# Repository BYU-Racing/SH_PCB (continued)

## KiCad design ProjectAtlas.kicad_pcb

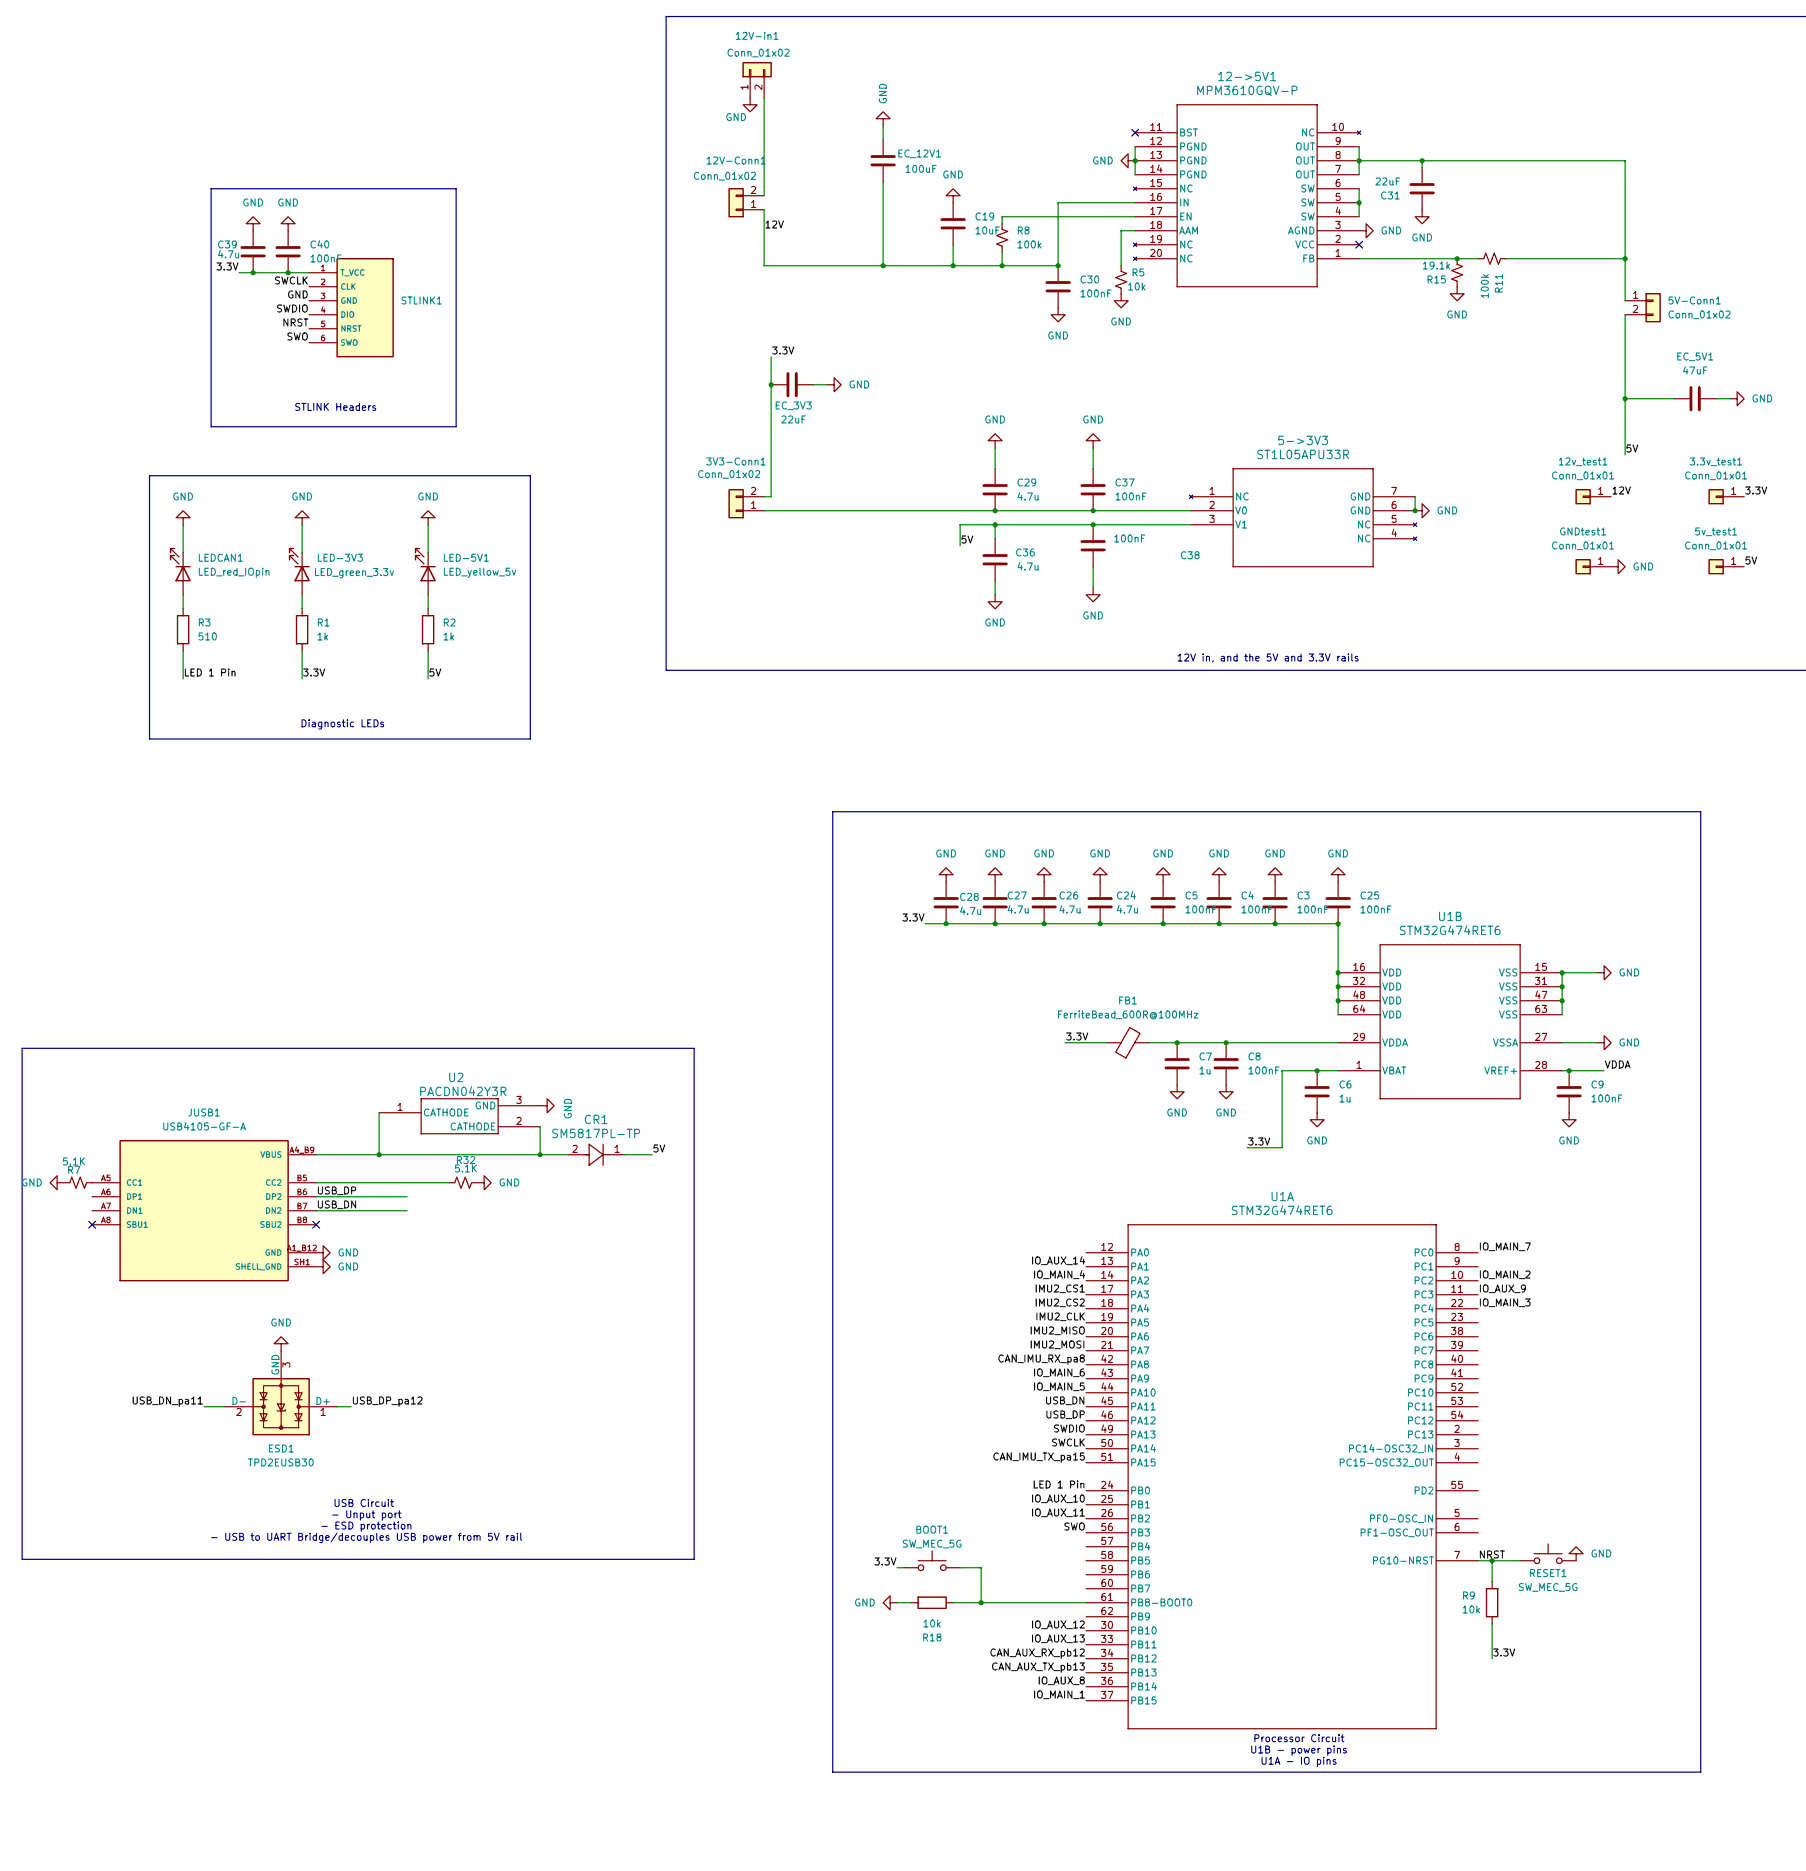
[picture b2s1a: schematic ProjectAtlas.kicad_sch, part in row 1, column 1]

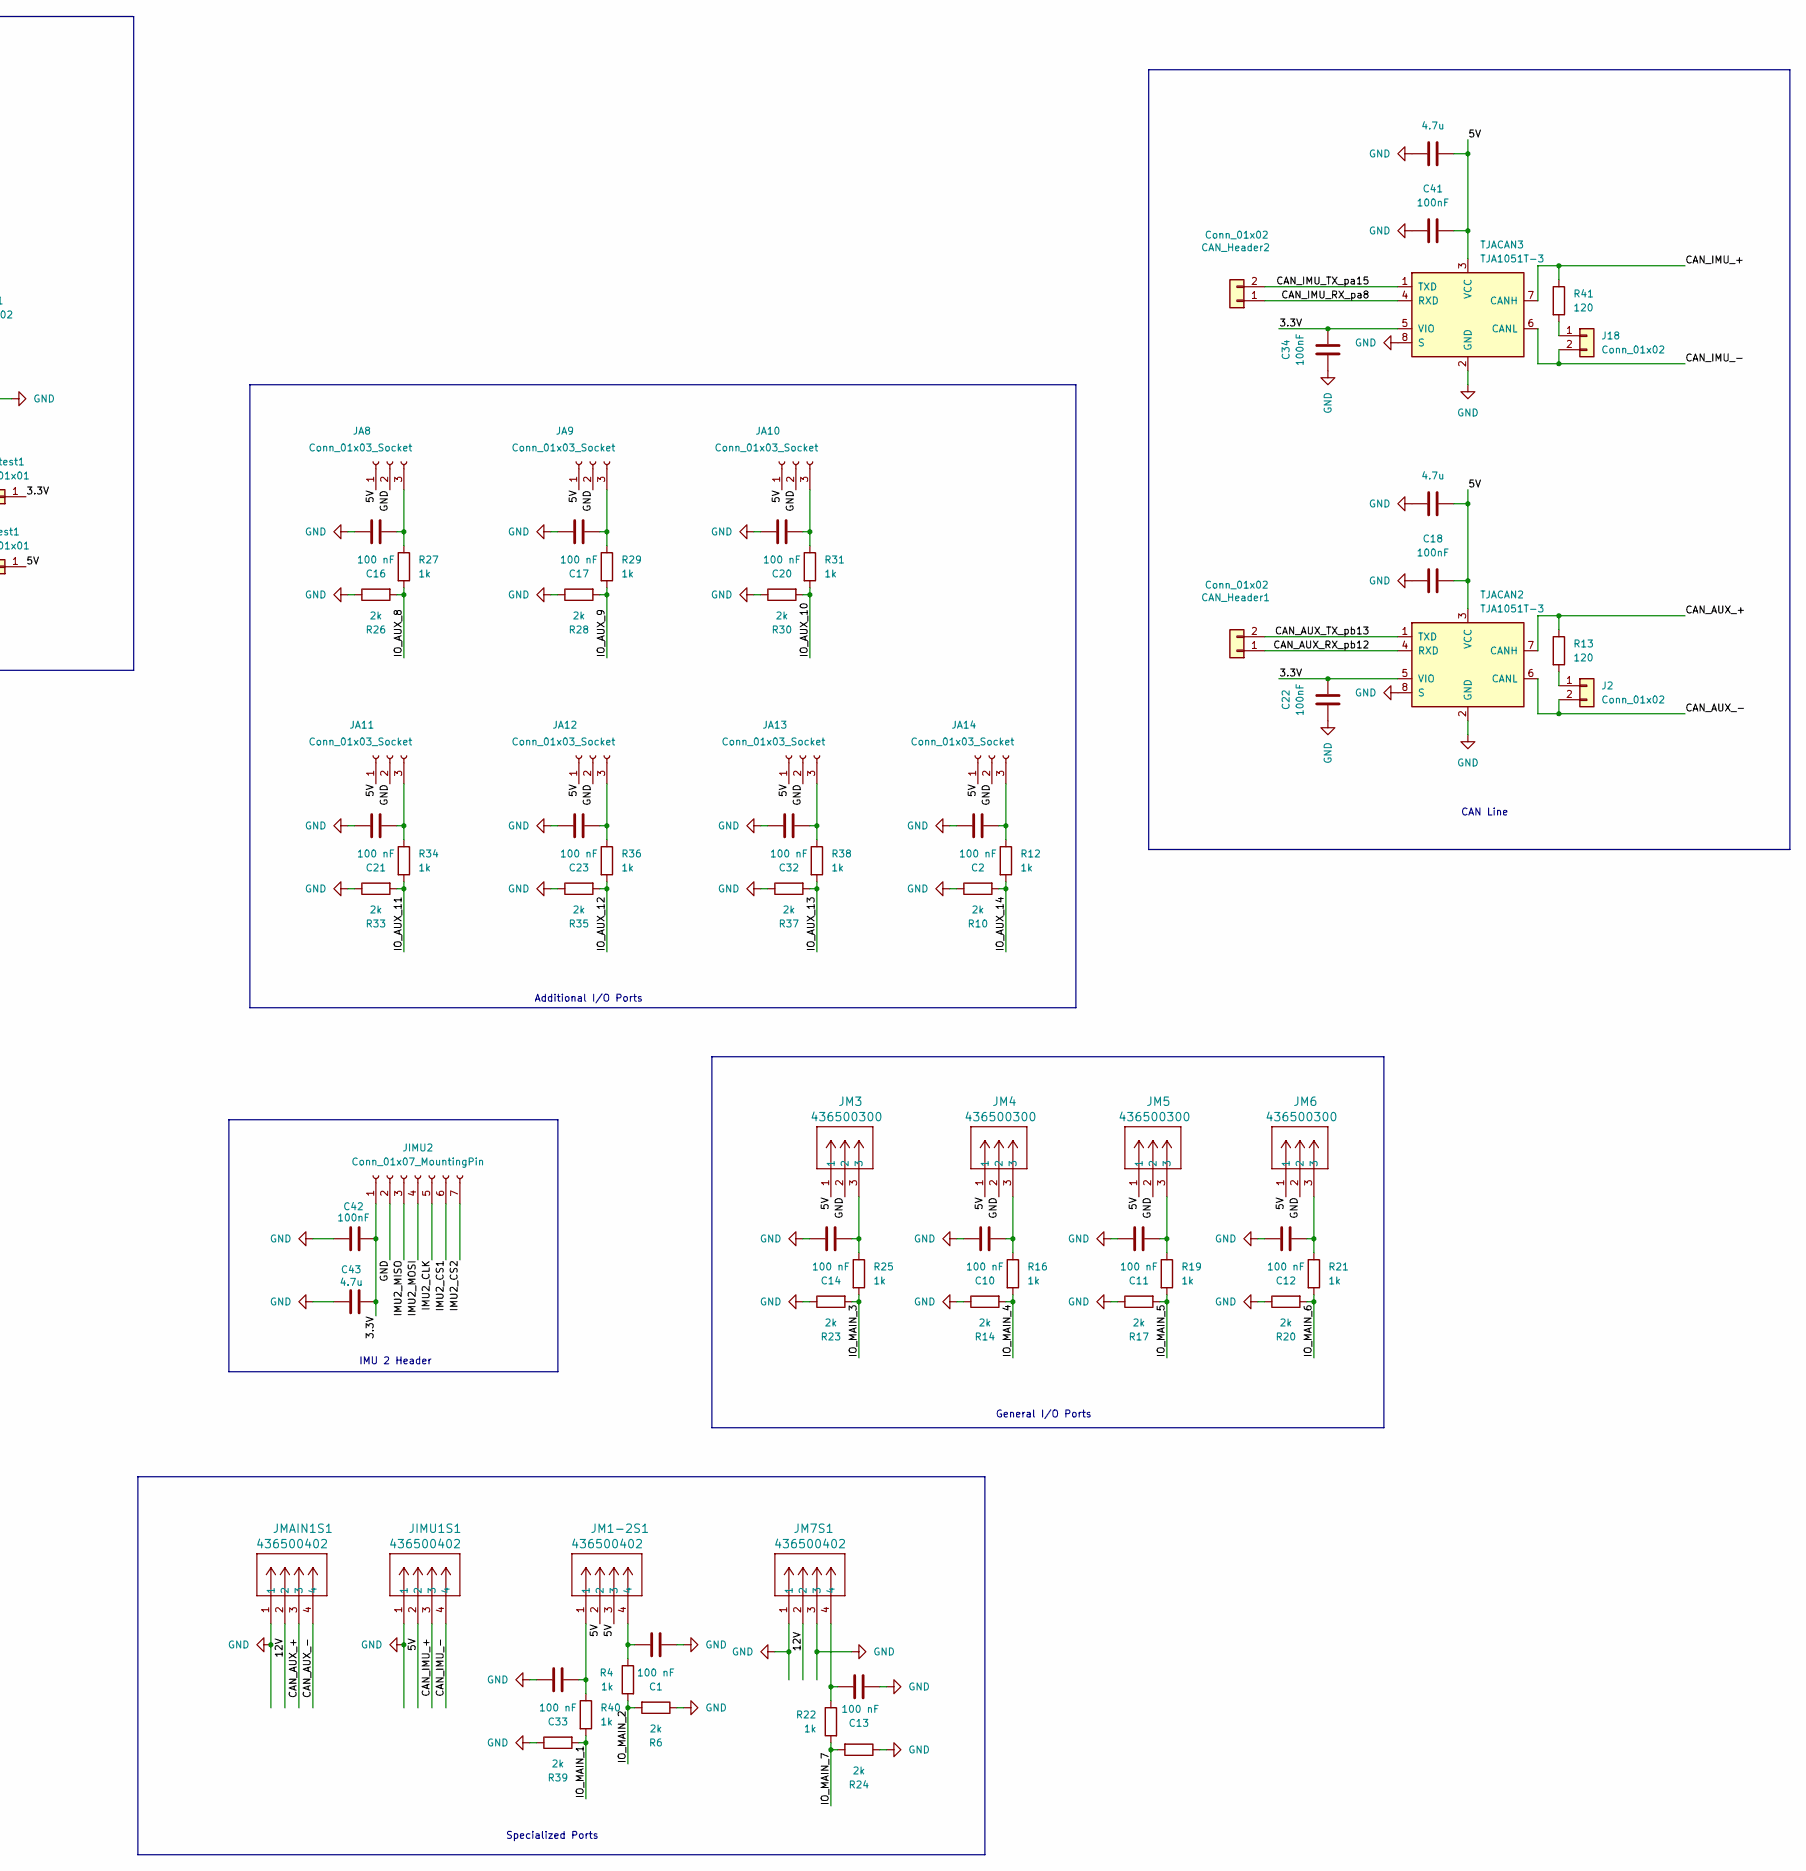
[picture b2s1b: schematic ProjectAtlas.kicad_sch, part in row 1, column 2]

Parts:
3.3v_test1, 5v_test1, 12v_test1: Conn_01x01; PinHeader_1x01_P2.54mm_Vertical
3V3-Conn1, 5V-Conn1, 12V-Conn1, 12V-in1: Conn_01x02; PinHeader_1x02_P2.54mm_Vertical
5->3V3: ST1L05APU33R; DFN_5APU33R_STM
12->5V1: MPM3610GQV-P
BOOT1: SW_MEC_5G; TS-1187A-B-A-B
C1, C2, C10, C11, C12, C13, C14, C16, C17, C20, C21, C23, C32, C33: 100 nF; CP_Axial_L10.0mm_D6.0mm_P15.00mm_Horizontal
C3, C4, C5, C8, C9, C18, C22, C25, C30, C34, C37, C38, C40, C41, C42: 100nF; C_0603_1608Metric
C6, C7: 1u; C_0805_2012Metric
C15, C24, C26, C27, C28, C29, C35, C36, C39, C43: 4.7u; C_0805_2012Metric
C19: 10uF; C_0805_2012Metric
C31: 22uF; C_0805_2012Metric
CAN_Header1, CAN_Header2: Conn_01x02; PinHeader_1x02_P2.54mm_Vertical
CR1: SM5817PL-TP
EC_3V3: 22uF; CP_Elec_4x5.4
EC_5V1: 47uF; CP_Elec_6.3x5.4
EC_12V1: 100uF; CP_Elec_8x10
ESD1: TPD2EUSB30; Texas_DRT-3
FB1: FerriteBead_600R@100MHz; GZ1608D601TF
GNDtest1: Conn_01x01; PinHeader_1x01_P2.54mm_Vertical
J2, J18: Conn_01x02; PinHeader_1x02_P2.54mm_Vertical
JA8, JA9, JA10, JA11, JA12, JA13, JA14: Conn_01x03_Socket; PinHeader_1x03_P2.00mm_Vertical
JIMU1S1: 436500402; CONN_SD-43650-001_04_MOL
JIMU2: Conn_01x07_MountingPin; PinHeader_1x07_P2.00mm_Vertical
JM1-2S1, JM7S1: 436500402; CONN_SD-43650-001_04_MOL
JM3, JM4, JM5, JM6: 436500300; CONN_SD-43650-001_03_MOL
JMAIN1S1: 436500402; CONN_SD-43650-001_04_MOL
JUSB1: USB4105-GF-A; GCT_USB4105-GF-A; PARTREV B4
LED-3V3: LED_green_3.3v; LED_0805_2012Metric
LED-5V1: LED_yellow_5v; LED_0805_2012Metric
LEDCAN1: LED_red_IOpin; LED_0805_2012Metric
R1, R2: 1k; R_0603_1608Metric
R3: 510; R_0603_1608Metric
R4, R12, R16, R19, R21, R22, R25, R27, R29, R31, R34, R36, R38, R40: 1k; R_Axial_DIN0204_L3.6mm_D1.6mm_P1.90mm_Vertical
R5, R9, R18: 10k; R_0603_1608Metric
R6, R10, R14, R17, R20, R23, R24, R26, R28, R30, R33, R35, R37, R39: 2k; R_Axial_DIN0204_L3.6mm_D1.6mm_P1.90mm_Vertical
R7, R32: 5.1K; R_0603_1608Metric
R8, R11: 100k; R_0603_1608Metric
R13, R41: 120; R_0603_1608Metric
R15: 19.1k; R_0603_1608Metric
RESET1: SW_MEC_5G; TS-1187A-B-A-B
STLINK1: PinHeader_1x06_P2.54mm_Vertical
TJACAN2, TJACAN3: TJA1051T-3; SOIC-8_3.9x4.9mm_P1.27mm
U1: STM32G474RET6; STM32G474RE
U2: PACDN042Y3R; SOT-23_ONS

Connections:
/3.3V: 3.3v_test1.1, 3V3-Conn1.2, BOOT1.3 (B), BOOT1.4 (B), C3.2, C4.2, C5.2, C6.1, C22.2, C24.2, C25.2, C26.2, C27.2, C28.2, C34.2, C39.2, C40.2, C42.2, C43.2, EC_3V3.1, FB1.1, JIMU2.1, R1.2, R9.1, STLINK1.1 (T_VCC), TJACAN2.5 (VIO), TJACAN3.5 (VIO), U1.1 (VBAT), U1.16 (VDD), U1.32 (VDD), U1.48 (VDD), U1.64 (VDD)
/5V: 5->3V3.3 (V1), 5V-Conn1.2, 5v_test1.1, C15.2, C18.2, C35.2, C36.1, C38.2, C41.2, CR1.1, EC_5V1.1, JA8.1, JA9.1, JA10.1, JA11.1, JA12.1, JA13.1, JA14.1, JIMU1S1.2, JM1-2S1.2, JM1-2S1.3, JM3.1, JM4.1, JM5.1, JM6.1, R2.2, TJACAN2.3 (VCC), TJACAN3.3 (VCC)
/12V: 12->5V1.16 (IN), 12V-Conn1.1, 12v_test1.1, C19.2, C30.1, EC_12V1.1, JM7S1.2, JMAIN1S1.2, R8.2
/CAN_AUX_+: JMAIN1S1.3, R13.1, TJACAN2.7 (CANH)
/CAN_AUX_-: J2.2, JMAIN1S1.4, TJACAN2.6 (CANL)
/CAN_AUX_RX_pb12: CAN_Header1.1, TJACAN2.4 (RXD), U1.34 (PB12)
/CAN_AUX_TX_pb13: CAN_Header1.2, TJACAN2.1 (TXD), U1.35 (PB13)
/CAN_IMU_+: JIMU1S1.3, R41.1, TJACAN3.7 (CANH)
/CAN_IMU_-: J18.2, JIMU1S1.4, TJACAN3.6 (CANL)
/CAN_IMU_RX_pa8: CAN_Header2.1, TJACAN3.4 (RXD), U1.42 (PA8)
/CAN_IMU_TX_pa15: CAN_Header2.2, TJACAN3.1 (TXD), U1.51 (PA15)
/IMU2_CLK: JIMU2.5, U1.19 (PA5)
/IMU2_CS1: JIMU2.6, U1.17 (PA3)
/IMU2_CS2: JIMU2.7, U1.18 (PA4)
/IMU2_MISO: JIMU2.3, U1.20 (PA6)
/IMU2_MOSI: JIMU2.4, U1.21 (PA7)
/IO_AUX_8: R26.2, R27.2, U1.36 (PB14)
/IO_AUX_9: R28.2, R29.2, U1.11 (PC3)
/IO_AUX_10: R30.2, R31.2, U1.25 (PB1)
/IO_AUX_11: R33.2, R34.2, U1.26 (PB2)
/IO_AUX_12: R35.2, R36.2, U1.30 (PB10)
/IO_AUX_13: R37.2, R38.2, U1.33 (PB11)
/IO_AUX_14: R10.2, R12.2, U1.13 (PA1)
/IO_MAIN_1: R39.2, R40.2, U1.37 (PB15)
/IO_MAIN_2: R4.2, R6.2, U1.10 (PC2)
/IO_MAIN_3: R23.2, R25.2, U1.22 (PC4)
/IO_MAIN_4: R14.2, R16.2, U1.14 (PA2)
/IO_MAIN_5: R17.2, R19.2, U1.44 (PA10)
/IO_MAIN_6: R20.2, R21.2, U1.43 (PA9)
/IO_MAIN_7: R22.2, R24.2, U1.8 (PC0)
/LED 1 Pin: R3.2, U1.24 (PB0)
/NRST: R9.2, RESET1.1 (A), RESET1.2 (A), STLINK1.5 (NRST), U1.7 (PG10-NRST)
/SWCLK: STLINK1.2 (CLK), U1.50 (PA14)
/SWDIO: STLINK1.4 (DIO), U1.49 (PA13)
/SWO: STLINK1.6 (SWO), U1.56 (PB3)
/USB_DN: JUSB1.B7 (DN2), U1.45 (PA11)
/USB_DN_pa11: ESD1.2 (D-)
/USB_DP: JUSB1.B6 (DP2), U1.46 (PA12)
/USB_DP_pa12: ESD1.1 (D+)
/VDDA: C9.1, U1.28 (VREF+)
GND: 5->3V3.6 (GND), 5->3V3.7 (GND), 12->5V1.3 (AGND), 12->5V1.12 (PGND), 12->5V1.13 (PGND), 12->5V1.14 (PGND), 12V-in1.1, C1.1, C2.1, C3.1, C4.1, C5.1, C6.2, C7.2, C8.2, C9.2, C10.1, C11.1, C12.1, C13.1, C14.1, C15.1, C16.1, C17.1, C18.1, C19.1, C20.1, C21.1, C22.1, C23.1, C24.1, C25.1, C26.1, C27.1, C28.1, C29.1, C30.2, C31.1, C32.1, C33.1, C34.1, C35.1, C36.2, C37.1, C38.1, C39.1, C40.1, C41.1, C42.1, C43.1, EC_3V3.2, EC_5V1.2, EC_12V1.2, ESD1.3 (GND), GNDtest1.1, JA8.2, JA9.2, JA10.2, JA11.2, JA12.2, JA13.2, JA14.2, JIMU1S1.1, JIMU2.2, JM3.2, JM4.2, JM5.2, JM6.2, JM7S1.1, JM7S1.3, JMAIN1S1.1, JUSB1.A1_B12 (GND), JUSB1.B1_A12 (GND), JUSB1.SH1 (SHELL_GND), JUSB1.SH2 (SHELL_GND), JUSB1.SH3 (SHELL_GND), JUSB1.SH4 (SHELL_GND), LED-3V3.1 (K), LED-5V1.1 (K), LEDCAN1.1 (K), R5.2, R6.1, R7.2, R10.1, R14.1, R15.1, R17.1, R18.2, R20.1, R23.1, R24.1, R26.1, R28.1, R30.1, R32.2, R33.1, R35.1, R37.1, R39.1, RESET1.3 (B), RESET1.4 (B), STLINK1.3 (GND), TJACAN2.2 (GND), TJACAN2.8 (S), TJACAN3.2 (GND), TJACAN3.8 (S), U1.15 (VSS), U1.27 (VSSA), U1.31 (VSS), U1.47 (VSS), U1.63 (VSS), U2.3 (GND)
unnamed: 3V3-Conn1.1, 5->3V3.2 (V0), C29.2, C37.2
unnamed: 5V-Conn1.1, 12->5V1.7 (OUT), 12->5V1.8 (OUT), 12->5V1.9 (OUT), C31.2, R11.1
unnamed: 12->5V1.18 (AAM), R5.1
unnamed: 12->5V1.17 (EN), R8.1
unnamed: 12->5V1.1 (FB), R11.2, R15.2
unnamed: 12->5V1.4 (SW), 12->5V1.5 (SW), 12->5V1.6 (SW)
unnamed: 12V-Conn1.2, 12V-in1.2
unnamed: C1.2, JM1-2S1.4, R4.1
unnamed: C10.2, JM4.3, R16.1
unnamed: C11.2, JM5.3, R19.1
unnamed: C12.2, JM6.3, R21.1
unnamed: C13.2, JM7S1.4, R22.1
unnamed: C14.2, JM3.3, R25.1
unnamed: C33.2, JM1-2S1.1, R40.1
unnamed: J2.1, R13.2
unnamed: J18.1, R41.2
unnamed: C16.2, JA8.3, R27.1
unnamed: C17.2, JA9.3, R29.1
unnamed: C20.2, JA10.3, R31.1
unnamed: C21.2, JA11.3, R34.1
unnamed: C23.2, JA12.3, R36.1
unnamed: C32.2, JA13.3, R38.1
unnamed: C2.2, JA14.3, R12.1
unnamed: JUSB1.A5 (CC1), R7.1
unnamed: JUSB1.B5 (CC2), R32.1
unnamed: LED-3V3.2 (A), R1.1
unnamed: LED-5V1.2 (A), R2.1
unnamed: LEDCAN1.2 (A), R3.1
unnamed: BOOT1.1 (A), BOOT1.2 (A), R18.1, U1.61 (PB8-BOOT0)
unnamed: C7.1, C8.1, FB1.2, U1.29 (VDDA)
VBUS: CR1.2, JUSB1.A4_B9 (VBUS), JUSB1.B4_A9 (VBUS), U2.1 (CATHODE), U2.2 (CATHODE)

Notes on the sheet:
General I/O Ports
USB Circuit - Unput port - ESD protection - USB to UART Bridge/decouples USB power from 5V rail
Specialized Ports
STLINK Headers
IMU 2 Header
12V in, and the 5V and 3.3V rails
Additional I/O Ports
Processor Circuit U1B - power pins U1A - IO pins
CAN Line
Diagnostic LEDs

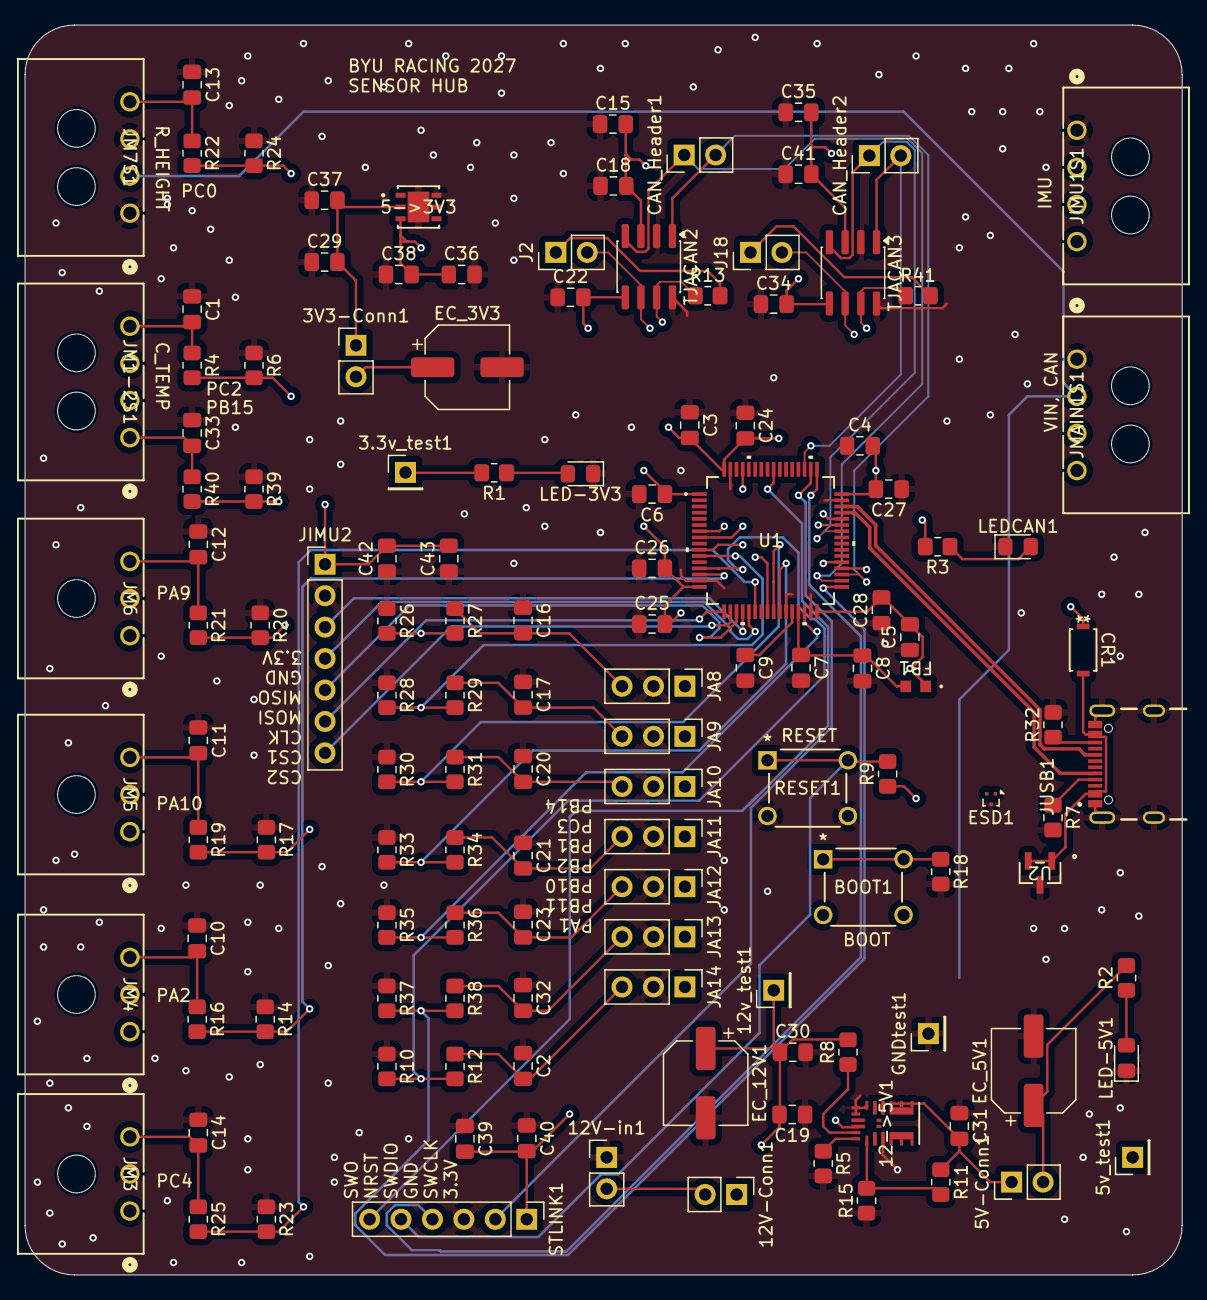
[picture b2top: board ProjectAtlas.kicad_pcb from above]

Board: 4 copper layers, 93.5 x 101.0 mm, 131 parts (0 on the bottom side), 70 nets.
